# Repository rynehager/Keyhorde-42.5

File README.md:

# Keyhorde-42.5
Babby's first bad keyboard PCB

This is a not-quite 40%, not-quite 50% keyboard being made for the founding members of Keyhorde with the following layout:

The purpose is to design a compact, USB Type-C caseless keyboard with a bare PCB aesthetic and a layout that doesn't interfere with general writing, including commonly used punctuation, but which is also as portable as possible and generally compatible with keyset options — i.e., it does not require custom or incorrect legend keys when using a set with wide compatibility. 

Schematics and layout designed in KiCAD, licensing CC0 so feel free to reuse, remix, make, sell, etc. whatever you dig bby just don't hold me responsible.

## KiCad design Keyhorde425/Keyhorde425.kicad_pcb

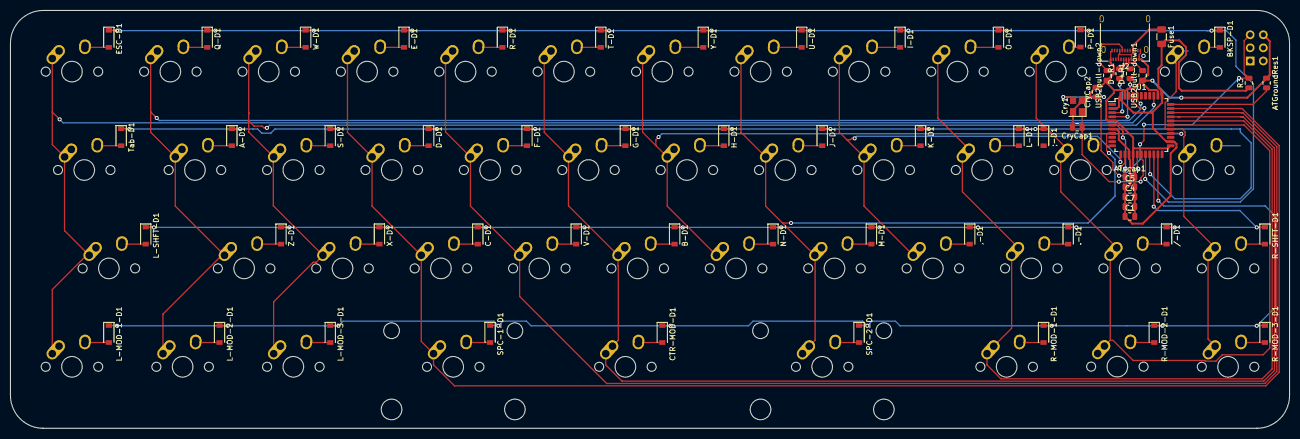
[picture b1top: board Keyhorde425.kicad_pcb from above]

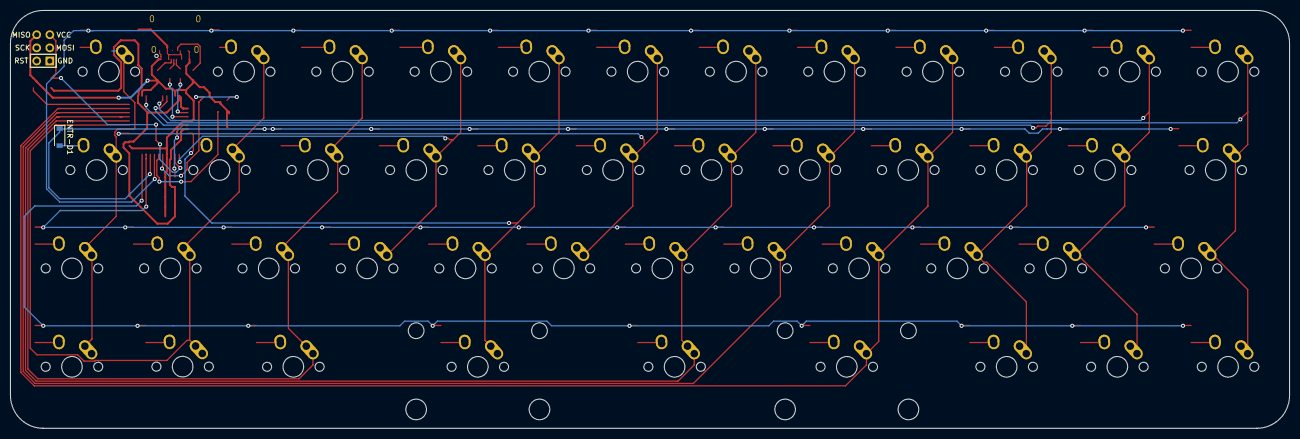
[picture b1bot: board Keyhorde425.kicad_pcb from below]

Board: 2 copper layers, 247.7 x 80.9 mm, 108 parts (2 on the bottom side), 74 nets.

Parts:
,-D1: SOD-123; D_SOD-123
,-key1: MX-NoLED; MX-1U-NoLED
.-D1: SOD-123; D_SOD-123
.-key1: MX-NoLED; MX-1U-NoLED
/-D1: SOD-123; D_SOD-123
/-key1: MX-NoLED; MX-1U-NoLED
;-D1: SOD-123; D_SOD-123
;-key1: MX-NoLED; MX-1U-NoLED
A-D1: SOD-123; D_SOD-123
A-key1: MX-NoLED; MX-1U-NoLED
ATGroundRes1: 10k; R_0805_2012Metric
ATucap1: 1uF; C_0805_2012Metric
B-D1: SOD-123; D_SOD-123
B-key1: MX-NoLED; MX-1U-NoLED
BKSP-D1: SOD-123; D_SOD-123
BKSP-key1: MX-NoLED; MX-1.75U-NoLED
C1, C4, C5: 0.1uf; C_0805_2012Metric
C7: 10uF; C_0805_2012Metric
C-D1: SOD-123; D_SOD-123
C-key1: MX-NoLED; MX-1U-NoLED
CTR-MOD-1: MX-NoLED; MX-1.25U-NoLED
CTR-MOD-D1: SOD-123; D_SOD-123
Cry1: 16MHz; Crystal_SMD_3225-4Pin_3.2x2.5mm
CryCap1, CryCap2: 22pF; C_0805_2012Metric
D+R1: 22; R_0805_2012Metric
D-D1: SOD-123; D_SOD-123
D-R1: 22; R_0805_2012Metric
D-key1: MX-NoLED; MX-1U-NoLED
E-D1: SOD-123; D_SOD-123
E-key1: MX-NoLED; MX-1U-NoLED
ENTR-D1: SOD-123; D_SOD-123
ENTR-key1: MX-NoLED; MX-1.5U-NoLED
ESC-D1: SOD-123; D_SOD-123
Esc-key1: MX-NoLED; MX-1U-NoLED
F-D1: SOD-123; D_SOD-123
F-key1: MX-NoLED; MX-1U-NoLED
Fuse1: 500mAh; Fuse_1206_3216Metric
G-D1: SOD-123; D_SOD-123
G-key1: MX-NoLED; MX-1U-NoLED
H-D1: SOD-123; D_SOD-123
H-key1: MX-NoLED; MX-1U-NoLED
I-D1: SOD-123; D_SOD-123
I-key1: MX-NoLED; MX-1U-NoLED
J2: USB_C_Receptacle_USB2.0; USB_C_Receptacle_Amphenol_12401610E4-2A
J-D1: SOD-123; D_SOD-123
J-key1: MX-NoLED; MX-1U-NoLED
K-D1: SOD-123; D_SOD-123
K-key1: MX-NoLED; MX-1U-NoLED
L-D1: SOD-123; D_SOD-123
L-MOD-1, L-MOD-3: MX-NoLED; MX-1U-NoLED
L-MOD-1-D1, L-MOD-2-D1, L-MOD-3-D1: SOD-123; D_SOD-123
L-MOD-2: MX-NoLED; MX-1.25U-NoLED
L-SHFT-D1: SOD-123; D_SOD-123
L-SHFT-key1: MX-NoLED; MX-1.75U-NoLED
L-key1: MX-NoLED; MX-1U-NoLED
M-D1: SOD-123; D_SOD-123
M-key1: MX-NoLED; MX-1U-NoLED
N-D1: SOD-123; D_SOD-123
N-key1: MX-NoLED; MX-1U-NoLED
O-D1: SOD-123; D_SOD-123
O-key1: MX-NoLED; MX-1U-NoLED
P-D1: SOD-123; D_SOD-123
P-key1: MX-NoLED; MX-1U-NoLED
Q-D1: SOD-123; D_SOD-123
Q-key1: MX-NoLED; MX-1U-NoLED
R3: 10k; R_0805_2012Metric
R-D1: SOD-123; D_SOD-123
R-MOD-1, R-MOD-3: MX-NoLED; MX-1U-NoLED
R-MOD-1-D1, R-MOD-2-D1, R-MOD-3-D1: SOD-123; D_SOD-123
R-MOD-2: MX-NoLED; MX-1.25U-NoLED
R-SHFT-D1: SOD-123; D_SOD-123
R-SHFT-key1: MX-NoLED; MX-1U-NoLED
R-key1: MX-NoLED; MX-1U-NoLED
S-D1: SOD-123; D_SOD-123
S-key1: MX-NoLED; MX-1U-NoLED
SPC-1: MX-NoLED; MX-2.25U-NoLED
SPC-1-D1, SPC-2-D1: SOD-123; D_SOD-123
SPC-2: MX-NoLED; MX-2.75U-NoLED
SW1: SW_Push; Reset_Pretty
T-D1: SOD-123; D_SOD-123
T-key1: MX-NoLED; MX-1U-NoLED
Tab-D1: SOD-123; D_SOD-123
Tab-key1: MX-NoLED; MX-1.25U-NoLED
U1: ATmega32U4-AU; LQFP-44_10x10mm_P0.8mm
U-D1: SOD-123; D_SOD-123
U-key1: MX-NoLED; MX-1U-NoLED
USB2pull-down1, USB2pull-down2: 5.1k; R_0805_2012Metric
V-D1: SOD-123; D_SOD-123
V-key1: MX-NoLED; MX-1U-NoLED
W-D1: SOD-123; D_SOD-123
Wkey1: MX-NoLED; MX-1U-NoLED
X-D1: SOD-123; D_SOD-123
X-key1: MX-NoLED; MX-1U-NoLED
Y-D1: SOD-123; D_SOD-123
Y-key1: MX-NoLED; MX-1U-NoLED
Z-D1: SOD-123; D_SOD-123
Z-key1: MX-NoLED; MX-1U-NoLED

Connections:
+5V: C1.1, C4.1, C5.1, C7.1, Fuse1.1, Fuse1.2, J2.A4, J2.A9, J2.B4, J2.B9, R3.1, U1.2, U1.7, U1.14, U1.24, U1.34, U1.44
COL0: Esc-key1.1, L-MOD-1.1, L-SHFT-key1.1, Tab-key1.1, U1.41
COL1: A-key1.1, L-MOD-2.1, Q-key1.1, U1.40, Z-key1.1
COL2: L-MOD-3.1, S-key1.1, U1.36, Wkey1.1, X-key1.1
COL3: C-key1.1, D-key1.1, E-key1.1, SPC-1.1, U1.32
COL4: F-key1.1, R-key1.1, U1.31, V-key1.1
COL5: B-key1.1, CTR-MOD-1.1, G-key1.1, T-key1.1, U1.30
COL6: H-key1.1, N-key1.1, U1.26, Y-key1.1
COL7: J-key1.1, M-key1.1, SPC-2.1, U1.8, U-key1.1
COL8: ,-key1.1, I-key1.1, K-key1.1, U1.12
COL9: .-key1.1, L-key1.1, O-key1.1, R-MOD-1.1, U1.29
COL10: /-key1.1, ;-key1.1, P-key1.1, R-MOD-2.1, U1.28
COL11: BKSP-key1.1, ENTR-key1.1, R-MOD-3.1, R-SHFT-key1.1, U1.27
D+: D+R1.2, J2.A6, J2.B6
D-: D-R1.2, J2.A7, J2.B7
GND: ATGroundRes1.1, ATucap1.2, C1.2, C4.2, C5.2, C7.2, Cry1.2, Cry1.4, CryCap1.2, CryCap2.2, J2.A1, J2.A12, J2.B1, J2.B12, SW1.1, U1.5, U1.15, U1.23, U1.35, U1.43, USB2pull-down1.1, USB2pull-down2.1
unnamed: ,-D1.2, ,-key1.2
unnamed: .-D1.2, .-key1.2
unnamed: /-D1.2, /-key1.2
unnamed: ;-D1.2, ;-key1.2
unnamed: A-D1.2, A-key1.2
unnamed: ATGroundRes1.2, U1.33
unnamed: ATucap1.1, U1.6
unnamed: B-D1.2, B-key1.2
unnamed: BKSP-D1.2, BKSP-key1.2
unnamed: C-D1.2, C-key1.2
unnamed: CTR-MOD-1.2, CTR-MOD-D1.2
unnamed: Cry1.1, CryCap1.1, U1.17
unnamed: Cry1.3, CryCap2.1, U1.16
unnamed: D+R1.1, U1.4
unnamed: D-D1.2, D-key1.2
unnamed: D-R1.1, U1.3
unnamed: E-D1.2, E-key1.2
unnamed: ENTR-D1.2, ENTR-key1.2
unnamed: ESC-D1.2, Esc-key1.2
unnamed: F-D1.2, F-key1.2
unnamed: G-D1.2, G-key1.2
unnamed: H-D1.2, H-key1.2
unnamed: I-D1.2, I-key1.2
unnamed: J2.A5, USB2pull-down1.2
unnamed: J2.B5, USB2pull-down2.2
unnamed: J-D1.2, J-key1.2
unnamed: K-D1.2, K-key1.2
unnamed: L-D1.2, L-key1.2
unnamed: L-MOD-1.2, L-MOD-1-D1.2
unnamed: L-MOD-2.2, L-MOD-2-D1.2
unnamed: L-MOD-3.2, L-MOD-3-D1.2
unnamed: L-SHFT-D1.2, L-SHFT-key1.2
unnamed: M-D1.2, M-key1.2
unnamed: N-D1.2, N-key1.2
unnamed: O-D1.2, O-key1.2
unnamed: P-D1.2, P-key1.2
unnamed: Q-D1.2, Q-key1.2
unnamed: R3.2, SW1.2, U1.13
unnamed: R-D1.2, R-key1.2
unnamed: R-MOD-1.2, R-MOD-1-D1.2
unnamed: R-MOD-2.2, R-MOD-2-D1.2
unnamed: R-MOD-3.2, R-MOD-3-D1.2
unnamed: R-SHFT-D1.2, R-SHFT-key1.2
unnamed: S-D1.2, S-key1.2
unnamed: SPC-1.2, SPC-1-D1.2
unnamed: SPC-2.2, SPC-2-D1.2
unnamed: T-D1.2, T-key1.2
unnamed: Tab-D1.2, Tab-key1.2
unnamed: U-D1.2, U-key1.2
unnamed: V-D1.2, V-key1.2
unnamed: W-D1.2, Wkey1.2
unnamed: X-D1.2, X-key1.2
unnamed: Y-D1.2, Y-key1.2
unnamed: Z-D1.2, Z-key1.2
ROW0: BKSP-D1.1, E-D1.1, ESC-D1.1, I-D1.1, O-D1.1, P-D1.1, Q-D1.1, R-D1.1, T-D1.1, U1.18, U-D1.1, W-D1.1, Y-D1.1
ROW1: ;-D1.1, A-D1.1, D-D1.1, ENTR-D1.1, F-D1.1, G-D1.1, H-D1.1, J-D1.1, K-D1.1, L-D1.1, S-D1.1, Tab-D1.1, U1.19
ROW2: ,-D1.1, .-D1.1, /-D1.1, B-D1.1, C-D1.1, L-SHFT-D1.1, M-D1.1, N-D1.1, R-SHFT-D1.1, U1.20, V-D1.1, X-D1.1, Z-D1.1
ROW3: CTR-MOD-D1.1, L-MOD-1-D1.1, L-MOD-2-D1.1, L-MOD-3-D1.1, R-MOD-1-D1.1, R-MOD-2-D1.1, R-MOD-3-D1.1, SPC-1-D1.1, SPC-2-D1.1, U1.21

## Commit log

2022-11-09 Initial commit with blank PCB files
    Add kicad pro and sch files.
2022-11-09 Add submodules as per guide
2022-11-09 Add footprint libraries
    Added and linked project-specific libraries for MX switches and other parts.
2022-11-09 Schematic first draft w/USB C
    First draft of the PCB schematic before layout. Basic conversion from Mini USB 2.0 to USB Type-C, unsure if correct/complete, unsure if column wiring to controller is correct, unsure if schematic nee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
2022-11-10 Updated schematic with bad diode footprint
2022-11-10 Add marbastlib submodule
2022-11-11 Halfway done routing traces (hopefully)
    Layout finished barring reset switch, a better Type-C port, and any issues. Begun routing.
2022-11-11 Added DigiKey library
    Hoping I can find a more compact USB Type-C port, but no luck so far.
2022-11-20 Take two on routing
    Wiped all routing and started over in preparation for wiping all routing and starting over again next time.
2022-11-27 First draft routing
    First draft of the PCB with certifiably bad routing complete. Still needs better USB Type-C footprint/receptacle
